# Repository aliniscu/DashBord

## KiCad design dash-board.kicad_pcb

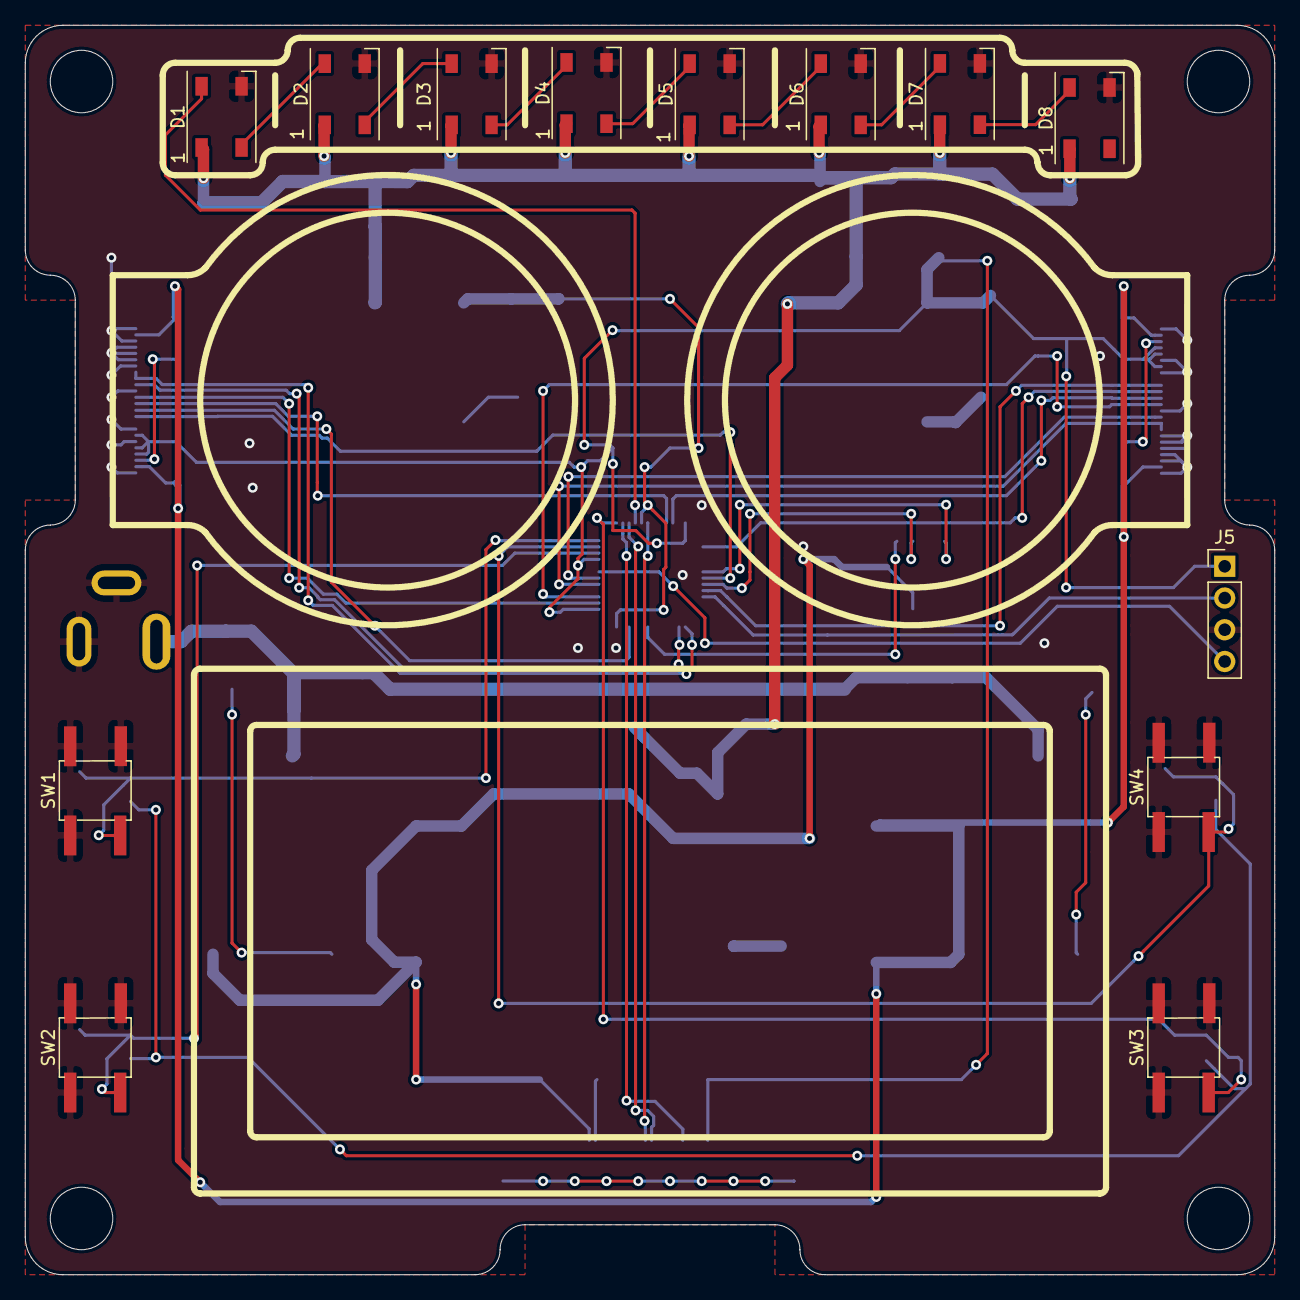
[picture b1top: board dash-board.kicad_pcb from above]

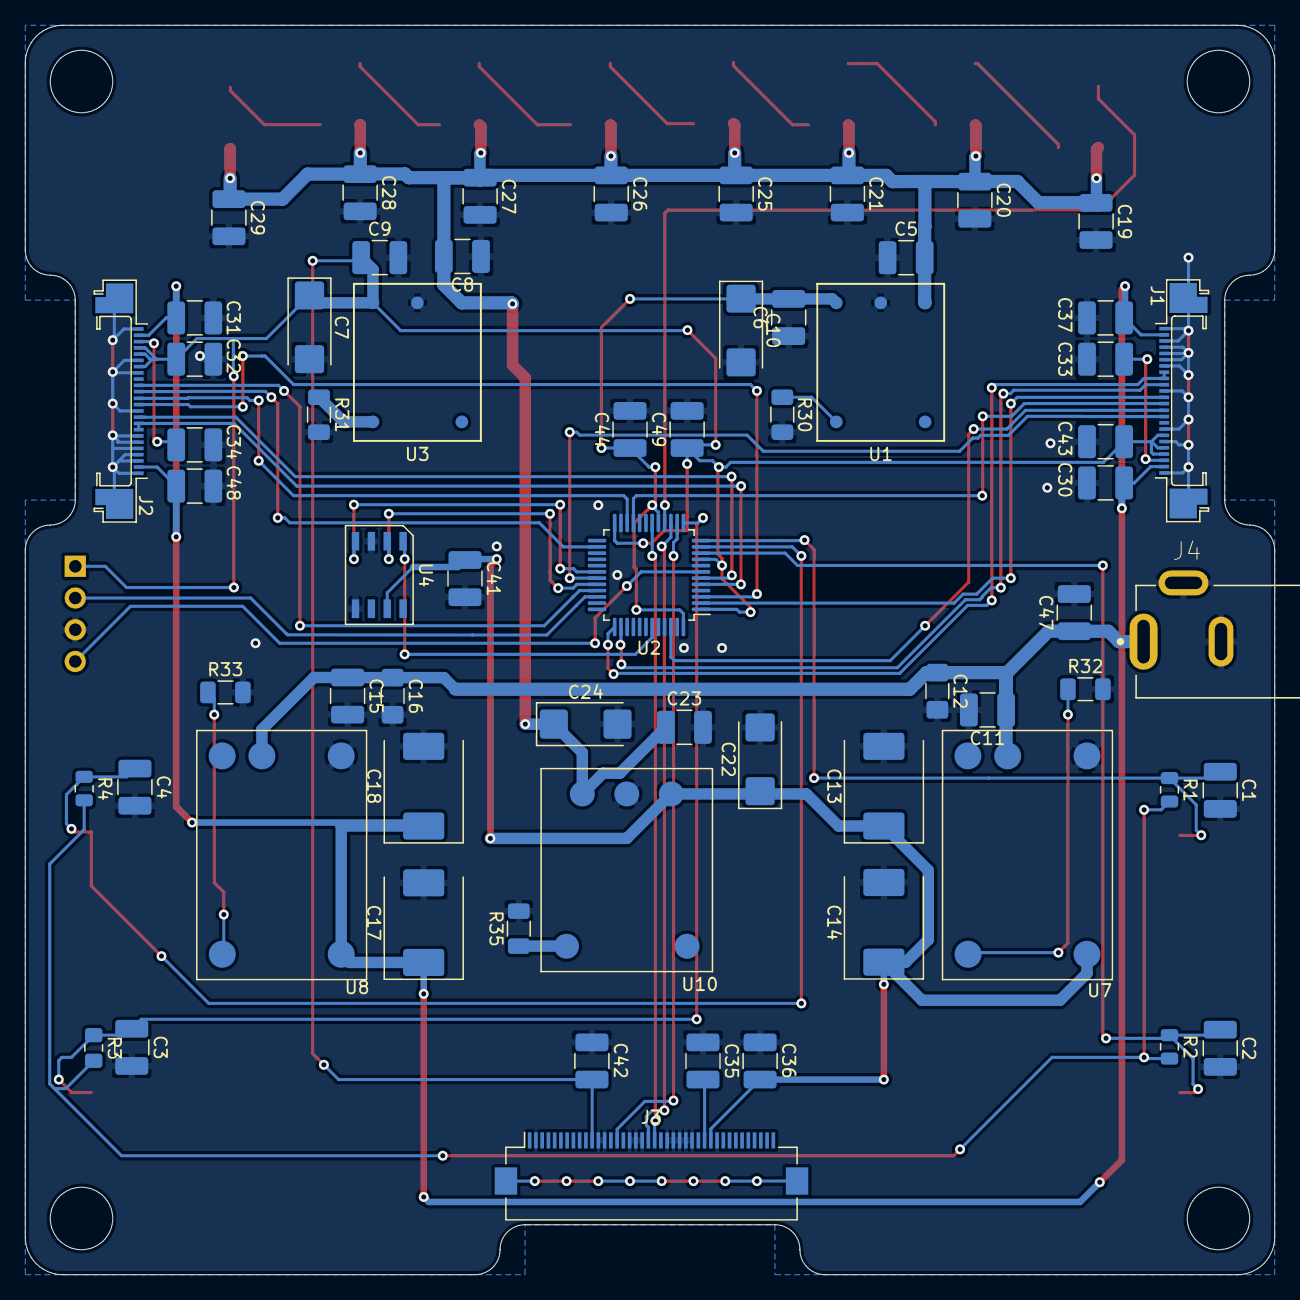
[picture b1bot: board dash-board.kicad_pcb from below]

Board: 2 copper layers, 100.0 x 100.0 mm, 77 parts (64 on the bottom side), 48 nets.

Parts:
C1, C2, C3, C4, C30, C31, C32, C34, C36, C37, C41, C42, C43, C44, C48, C49: 20u; C_1210_3225Metric_Pad1.42x2.65mm_HandSolder
C5, C6, C8, C9, C23: 47U; C_1210_3225Metric_Pad1.42x2.65mm_HandSolder
C7, C10, C22, C24: 47U; CP_EIA-6032-28_Kemet-C_Pad2.25x2.35mm_HandSolder
C11, C15: 10U; C_1210_3225Metric_Pad1.42x2.65mm_HandSolder
C12, C16: 2.2U; C_1206_3216Metric_Pad1.42x1.75mm_HandSolder
C13, C14, C17, C18: 100U; CP_EIA-7361-38_AVX-V_Pad2.18x3.30mm_HandSolder
C19, C20, C21, C25, C26, C27, C28, C29: C; C_1210_3225Metric_Pad1.42x2.65mm_HandSolder
C33, C35, C47: 100n; C_1210_3225Metric_Pad1.42x2.65mm_HandSolder
D1, D2, D3, D4, D5, D6, D7, D8: WS2812B; LED_WS2812B_PLCC4_5.0x5.0mm_P3.2mm
J1, J2: Conn_01x24_ROUND; molex-52437-2471
J3: Conn_01x31_SQWARE; Hirose_FH12-40S-0.5SH_1x40-1MP_P0.50mm_Horizontal
J4: KLDX-0202-AC; KYCON_KLDX-0202-AC
J5: Conn_01x04_Male; PinHeader_1x04_P2.54mm_Vertical
R1, R2, R4: R; R_0805_2012Metric
R3: R; R_0805_2012Metric_Pad1.15x1.40mm_HandSolder
R30: 6.6k; R_1206_3216Metric
R31: 475; R_1206_3216Metric
R32: 383K; R_1206_3216Metric
R33: 15k; R_1206_3216Metric
R35: 348; R_1206_3216Metric
SW1, SW2, SW3, SW4: SW_Push; SW_EVQQ2Y03W
U1, U3: PTH04070WAZ
U2: STM32F378CCTx; LQFP-48_7x7mm_P0.5mm
U4: MCP2003
U7, U8: PTN78000HAZ
U10: PTH08080W

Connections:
(SA0)_Round1: J1.12, U2.21
(SA0)_Round2: J2.12, U2.22
+1V8: C6.1, C10.1, C44.1, U1.3, U2.17, U2.48
+3V3: C7.1, C9.1, C32.1, C42.1, C43.1, C49.1, J1.4, J1.5, J1.7, J2.4, J2.5, J2.7, J3.11, J5.1, U2.1, U2.9, U2.24, U3.3
+5V: C5.1, C8.1, C19.1, C20.1, C21.1, C23.1, C24.1, C25.1, C26.1, C27.1, C28.1, C29.1, D1.1, D2.1, D3.1, D4.1, D5.1, D6.1, D7.1, D8.1, U1.1, U3.1, U10.3
+12V: C13.1, C14.1, C22.1, C36.1, C41.1, J3.30, U4.7, U7.5, U10.1
+15V: C17.1, C18.1, C30.1, C31.1, C37.1, C48.1, J1.2, J1.23, J2.2, J2.23, U8.5
+24V: C11.1, C12.1, C15.1, C16.1, C47.1, J4.1, U7.2, U8.2
GND: C1.2, C2.2, C3.2, C4.2, C5.2, C6.2, C7.2, C8.2, C9.2, C10.2, C11.2, C12.2, C13.2, C14.2, C15.2, C16.2, C17.2, C18.2, C19.2, C20.2, C21.2, C22.2, C23.2, C24.2, C25.2, C26.2, C27.2, C28.2, C29.2, C30.2, C31.2, C32.2, C33.1, C34.1, C35.1, C36.2, C37.2, C41.2, C42.2, C43.2, C44.2, C47.2, C48.2, C49.2, D1.3, D2.3, D3.3, D4.3, D5.3, D6.3, D7.3, D8.3, J1.1, J1.6, J1.8, J1.14, J1.18, J1.19, J1.20, J1.21, J1.22, J1.24, J2.1, J2.6, J2.8, J2.14, J2.18, J2.19, J2.20, J2.21, J2.22, J2.24, J3.2, J3.12, J3.13, J3.17, J3.18, J3.19, J3.23, J3.24, J3.25, J3.26, J3.27, J3.31, J4.2, J4.3, J5.3, R30.1, R31.2, R32.2, R33.2, R35.2, SW1.1, SW2.1, SW3.1, SW4.1, U1.2, U2.8, U2.23, U2.47, U3.2, U4.3, U4.5, U7.1, U8.1, U10.2
GPIO_Out_CS1: J1.10, U2.31
GPIO_Out_CS2: J2.10, U2.33
MISO: J5.2, U2.34
MOSI: J3.21, U2.18
NRST: J5.4, U2.7
NSS: J3.15, U2.14
unnamed: C1.1, R1.1, SW1.2, U2.12
unnamed: C2.1, R2.1, SW2.2, U2.10
unnamed: C3.1, R3.1, SW3.2, U2.13
unnamed: C4.1, R4.1, SW4.2, U2.11
unnamed: C33.2, J1.3
unnamed: C34.2, J2.3
unnamed: C35.2, J3.29
unnamed: D1.2, D2.4
unnamed: D1.4, U2.16
unnamed: D2.2, D3.4
unnamed: D3.2, D4.4
unnamed: D4.2, D5.4
unnamed: D5.2, D6.4
unnamed: D6.2, D7.4
unnamed: D7.2, D8.4
unnamed: R1.2, R2.2, R3.2, R4.2
unnamed: R30.2, U1.4
unnamed: R31.1, U3.4
unnamed: R32.1, U7.4
unnamed: R33.1, U8.4
unnamed: R35.1, U10.4
unnamed: U2.32, U4.2
RES_Round1: J1.11, U2.46
RES_Round2: J2.11, U2.26
SCK: J3.20, U2.15
SCL1: J1.15, U2.38
SCL2: J2.15, U2.6
SDA1: J1.16, J1.17, U2.37
SDA2: J2.16, J2.17, U2.5
USART1_Rx_LIN: U2.43, U4.1
USART1_Tx_LIN: U2.30, U4.4
WR_Round1: J1.13, U2.2
WR_Round2: J2.13, U2.3

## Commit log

2019-04-24 Initial Dash Project Kicad
2019-04-24 added todo file
2019-04-24 Added symbol lib
2019-04-26 Connector Molex
2019-04-29 molex V2
2019-04-29 TLE 9262 V1
2019-04-30 TLE 9262 V2
2019-04-30 TLE9262 V2.1
2019-04-30 TLE 9262 V2.1.1
2019-05-01 board outline defined
2019-05-01 modified footprints, added additional layers
2019-05-02 Auto stash before merge of "master" and "origin/master"
2019-05-02 LM4600
2019-05-06 some work on schematic
2019-06-22 added leds and shift registers
2019-07-05 Name Changes
2020-04-23 Last Update 23.04- Verificare butoane/VCC_conn/SWD_conn/Layout
2020-04-26 Update 26.04
    Layout v2
2020-05-11 Final Layout
    - debug pins
2020-05-13 layout changes
2020-05-13 layout final 2.0
2020-05-13 Generated fabrication files
2020-05-13 Regenerated fabrication files
